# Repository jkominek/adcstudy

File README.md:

# what is this?

A set of kicad 8 boards for investigating various combinations of ADC
and analog frontend for my [piano
conversion](https://github.com/jkominek/piano-conversion) project.

There might be some errors and problems with them, but I'm not currently
aware of any issues.

# please describe the boards

The ADC boards are designed to plug into a [Glasgow Interface
Explorer](https://glasgow-embedded.org/latest/intro.html), but that's
done via 2.54mm pin headers, so you can hook them up to anything with
some jumper wires. The Glasgow header has the various digital signals
necessary for the board, and provides VDD. (Which the Glasgow can adjust.)
Whichever of my applets are complete-enough are available in
[my fork of the Glasgow repo](https://github.com/jkominek/glasgow).

The other side of the ADC board is designed to plug into an analog
frontend board. It should provide VAA to the AFE board, and receives
back Vref, and AINx+ and AINx-. + and/or - might be Vref, or ground,
or whatever. The ADC board might also ignore one or of the two and
reference the other to... whatever it wants. The MCP3008 board for
instance uses AINx- only, and references GND and Vref.

The AFE boards take in VAA, and produce Vref, along with the Ax+ and Ax-
signals. One of them will probably be fixed. In the middle it can do
whatever it wants, and then the other end should be a 2x8 connector
which (in my application) is used for 8 phototransistors. The positive
pin of each pair is intended for the collector, and the negative pin
for the emitter.

You can of course plug whatever you want into those pins.

# what's wrong with them

Haven't tested the ADS131M08 or resistor ladder boards yet,
though I did correct the systemic issues of which I was aware.

# what choices do the boards give me

You can put the headers on in whichever orientation you want, though if
you're hooking it up to a Glasgow like I am, there are only a couple
options that make sense.

The opamp footprint is the most common four amp footprint, so you can
stick any of a bunch of opamps in there.

There are a number of voltage reference ICs that'll work in the provided
footprint. I've been putting on MIC5366-2.0 because I have a bunch of
them.

The MCP3008 board lets you feed VDD through to VAA with just some passive
filtering, or you can put in a linear regulator.

Obviously you can swap the gain setting resistors.

# quick what's best

For these sorts of signals, the MCP6L04 seems good enough, with the
TSV994 probably a runner up because it is more expensive. A ~2870ohm
thin film gain resistor and a capacitor in parallel with that resistor
which is in the ballpark of 10nF. A bias resistor of about 470k to drain
off dark current is also indicated.

I've got some more ideas for tweaking the TIA configuration with just
passives.

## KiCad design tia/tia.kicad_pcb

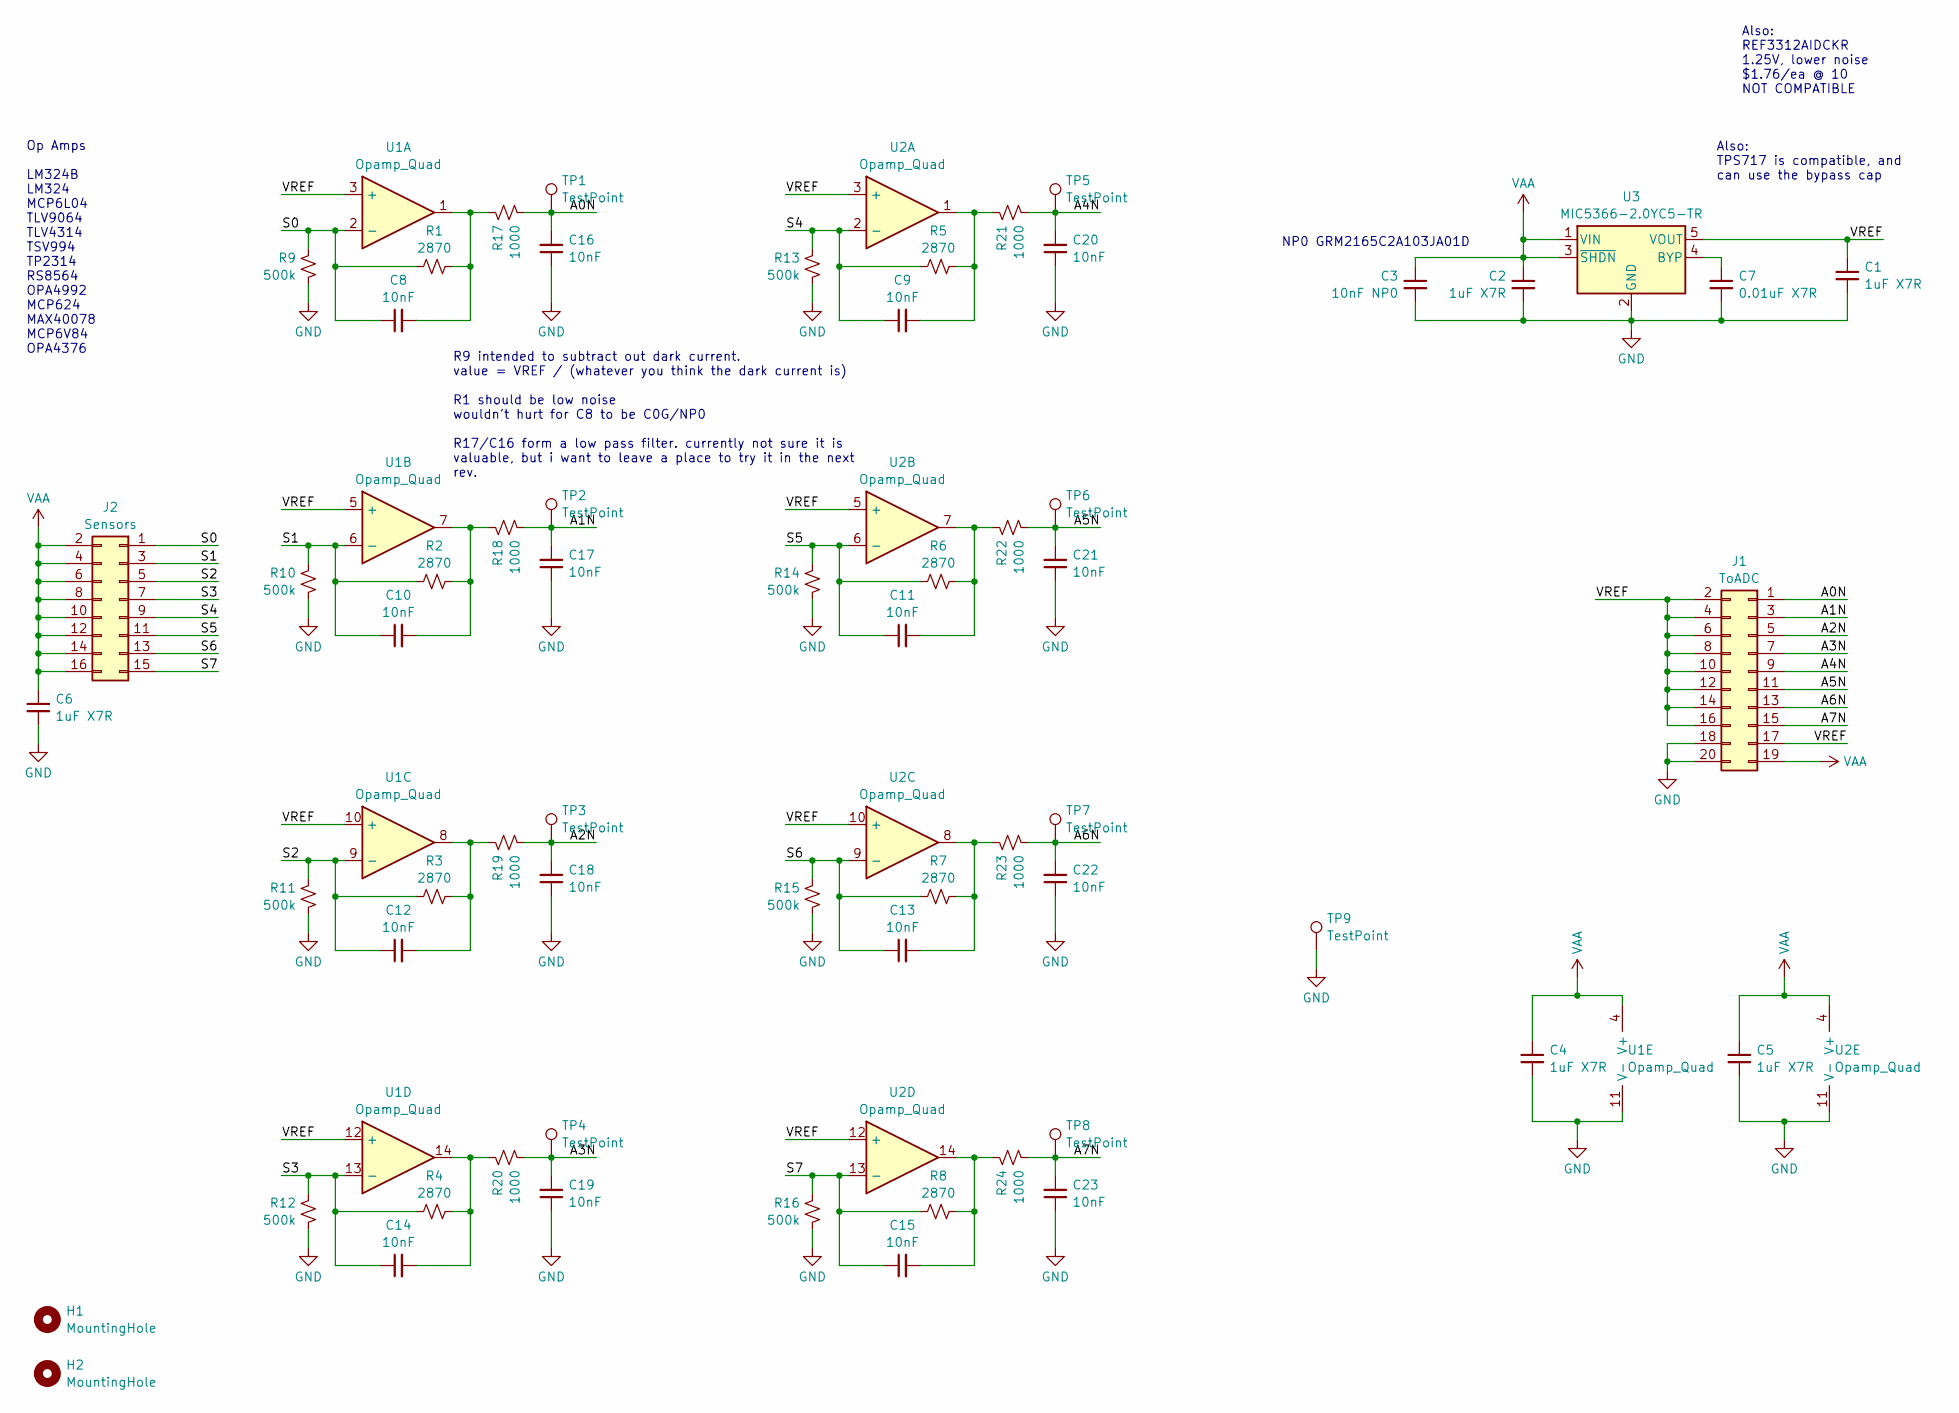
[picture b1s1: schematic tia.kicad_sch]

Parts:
C1, C2, C4, C5, C6: 1uF X7R; C_0805_2012Metric
C3: 10nF NP0; C_0805_2012Metric
C7: 0.01uF X7R; C_0805_2012Metric
C8, C9, C10, C11, C12, C13, C14, C15, C16, C17, C18, C19, C20, C21, C22, C23: 10nF; C_0805_2012Metric
H1, H2: MountingHole; MountingHole_3.2mm_M3
J1: ToADC; PinSocket_2x10_P2.54mm_Vertical
J2: Sensors; PinSocket_2x08_P2.54mm_Vertical
R1, R2, R3, R4, R5, R6, R7, R8: 2870; R_0805_2012Metric
R9, R10, R11, R12, R13, R14, R15, R16: 500k; R_0805_2012Metric
R17, R18, R19, R20, R21, R22, R23, R24: 1000; R_0805_2012Metric
TP1, TP2, TP3, TP4, TP5, TP6, TP7, TP8, TP9: TestPoint; TestPoint_Pad_D2.0mm
U1, U2: Opamp_Quad; TSSOP-14_4.4x5mm_P0.65mm
U3: MIC5366-2.0YC5-TR; SOT-353_SC-70-5

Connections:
/A0N: C16.2, J1.1, R17.1, TP1.1
/A1N: C17.2, J1.3, R18.1, TP2.1
/A2N: C18.2, J1.5, R19.1, TP3.1
/A3N: C19.2, J1.7, R20.1, TP4.1
/A4N: C20.2, J1.9, R21.1, TP5.1
/A5N: C21.2, J1.11, R22.1, TP6.1
/A6N: C22.2, J1.13, R23.1, TP7.1
/A7N: C23.2, J1.15, R24.1, TP8.1
/S0: C8.1, J2.1, R1.1, R9.2, U1.2 (-)
/S1: C10.1, J2.3, R2.1, R10.2, U1.6 (-)
/S2: C12.1, J2.5, R3.1, R11.2, U1.9 (-)
/S3: C14.1, J2.7, R4.1, R12.2, U1.13 (-)
/S4: C9.1, J2.9, R5.1, R13.2, U2.2 (-)
/S5: C11.1, J2.11, R6.1, R14.2, U2.6 (-)
/S6: C13.1, J2.13, R7.1, R15.2, U2.9 (-)
/S7: C15.1, J2.15, R8.1, R16.2, U2.13 (-)
/VREF: C1.1, J1.2, J1.4, J1.6, J1.8, J1.10, J1.12, J1.14, J1.16, J1.17, U1.3 (+), U1.5 (+), U1.10 (+), U1.12 (+), U2.3 (+), U2.5 (+), U2.10 (+), U2.12 (+), U3.5 (VOUT)
GND: C1.2, C2.2, C3.2, C4.2, C5.2, C6.2, C7.2, C16.1, C17.1, C18.1, C19.1, C20.1, C21.1, C22.1, C23.1, J1.18, J1.20, R9.1, R10.1, R11.1, R12.1, R13.1, R14.1, R15.1, R16.1, TP9.1, U1.11 (V-), U2.11 (V-), U3.2 (GND)
unnamed: C8.2, R1.2, R17.2, U1.1
unnamed: C9.2, R5.2, R21.2, U2.1
unnamed: C10.2, R2.2, R18.2, U1.7
unnamed: C11.2, R6.2, R22.2, U2.7
unnamed: C12.2, R3.2, R19.2, U1.8
unnamed: C13.2, R7.2, R23.2, U2.8
unnamed: C14.2, R4.2, R20.2, U1.14
unnamed: C15.2, R8.2, R24.2, U2.14
unnamed: C7.1, U3.4 (BYP)
VAA: C2.1, C3.1, C4.1, C5.1, C6.1, J1.19, J2.2, J2.4, J2.6, J2.8, J2.10, J2.12, J2.14, J2.16, U1.4 (V+), U2.4 (V+), U3.1 (VIN), U3.3 (~SHDN)

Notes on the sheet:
R9 intended to subtract out dark current. value = VREF / (whatever you think the dark current is) R1 should be low noise wouldn't hurt for C8 to be C0G/NP0 R17/C16 form a low pass filter. currently not sure it is valuable, but i want to leave a place to try it in the next rev.
Also: TPS717 is compatible, and can use the bypass cap
Also: REF3312AIDCKR 1.25V, lower noise $1.76/ea @ 10 NOT COMPATIBLE
Op Amps LM324B LM324 MCP6L04 TLV9064 TLV4314 TSV994 TP2314 RS8564 OPA4992 MCP624 MAX40078 MCP6V84 OPA4376
NP0 GRM2165C2A103JA01D

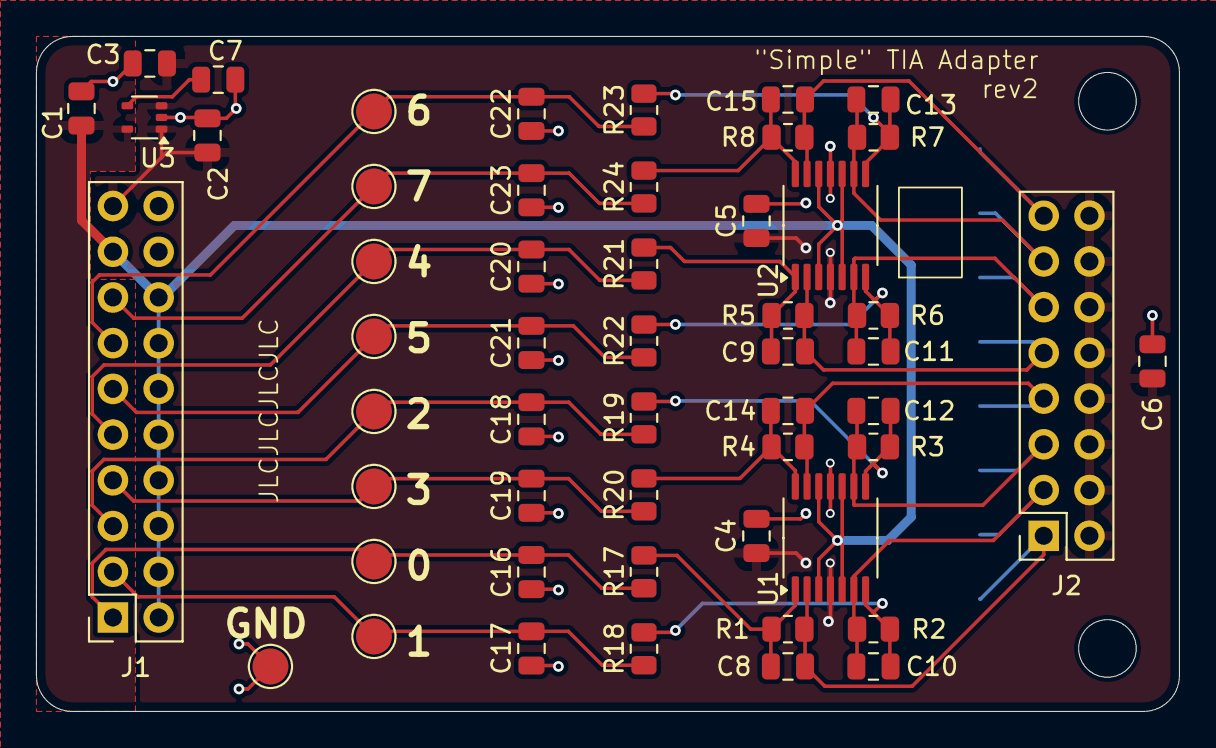
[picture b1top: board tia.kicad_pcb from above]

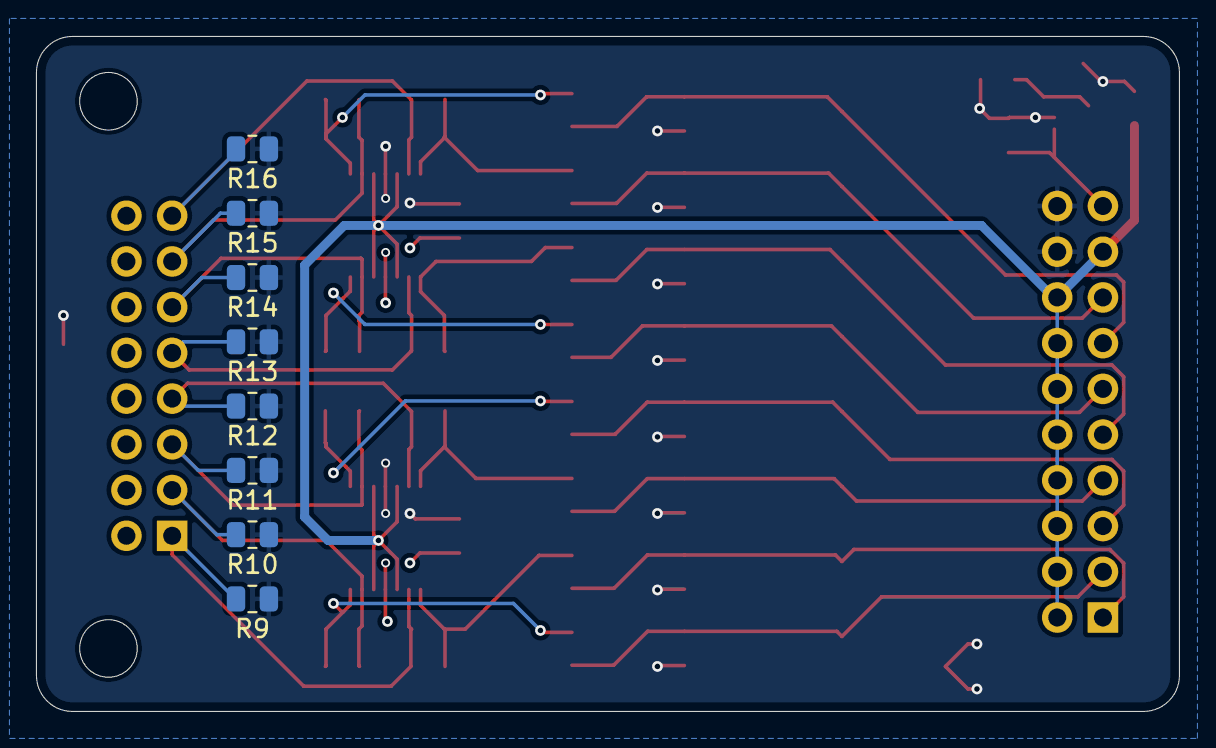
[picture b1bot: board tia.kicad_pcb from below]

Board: 4 copper layers, 63.5 x 37.5 mm, 63 parts (8 on the bottom side), 28 nets.

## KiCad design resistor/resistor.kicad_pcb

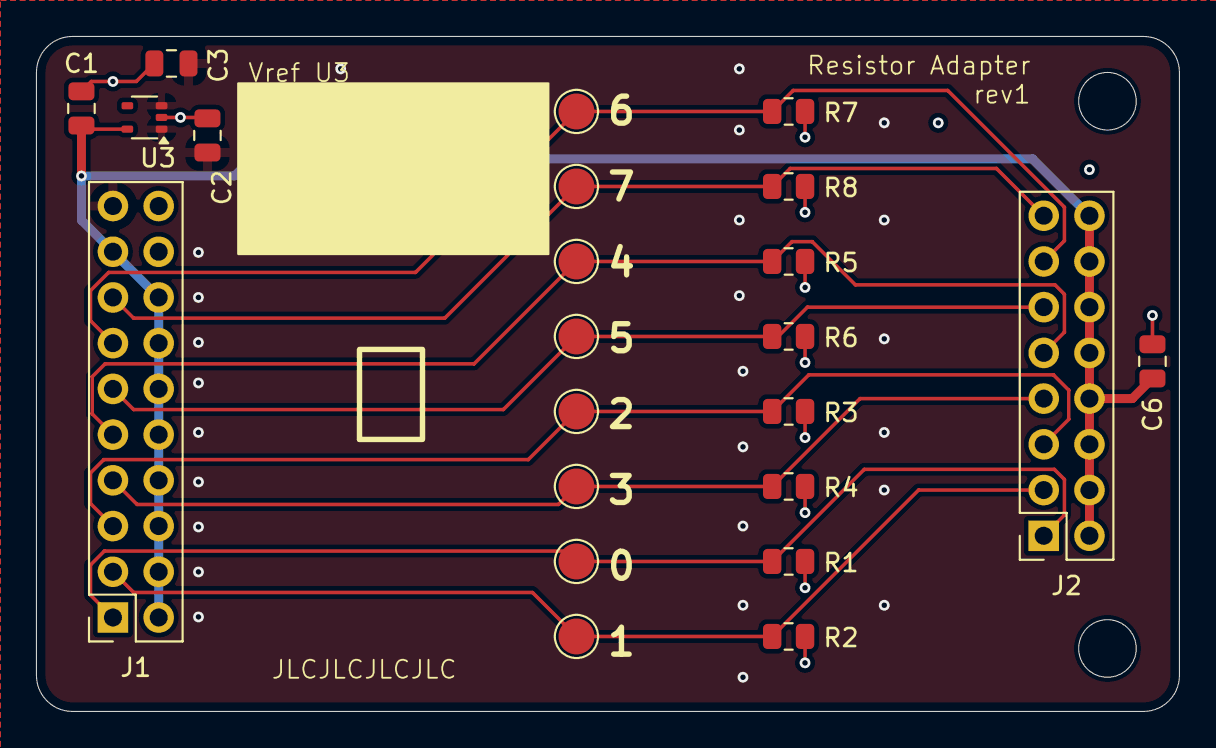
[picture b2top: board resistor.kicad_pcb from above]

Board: 4 copper layers, 63.5 x 37.5 mm, 25 parts (0 on the bottom side), 11 nets.

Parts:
C1, C2, C6: 1uF X7R; C_0805_2012Metric
C3: 10nF NP0; C_0805_2012Metric
H1, H2: MountingHole; MountingHole_3.2mm_M3
J1: ToADC; PinSocket_2x10_P2.54mm_Vertical
J2: Sensors; PinSocket_2x08_P2.54mm_Vertical
R1, R2, R3, R4, R5, R6, R7, R8: 1k; R_0805_2012Metric
TP1, TP2, TP3, TP4, TP5, TP6, TP7, TP8: TestPoint; TestPoint_Pad_D2.0mm
U3: MIC5366-2.0YC5-TR; SOT-353_SC-70-5

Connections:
/S0: J1.1, J2.1, R1.1, TP1.1
/S1: J1.3, J2.3, R2.1, TP2.1
/S2: J1.5, J2.5, R3.1, TP3.1
/S3: J1.7, J2.7, R4.1, TP4.1
/S4: J1.9, J2.9, R5.1, TP5.1
/S5: J1.11, J2.11, R6.1, TP6.1
/S6: J1.13, J2.13, R7.1, TP7.1
/S7: J1.15, J2.15, R8.1, TP8.1
/VREF: C1.1, C6.1, J1.2, J1.4, J1.6, J1.8, J1.10, J1.12, J1.14, J1.16, J1.17, J2.2, J2.4, J2.6, J2.8, J2.10, J2.12, J2.14, J2.16, U3.5 (VOUT)
GND: C1.2, C2.2, C3.2, C6.2, J1.18, J1.20, R1.2, R2.2, R3.2, R4.2, R5.2, R6.2, R7.2, R8.2, U3.2 (GND)
VAA: C2.1, C3.1, J1.19, U3.1 (VIN), U3.3 (~SHDN)

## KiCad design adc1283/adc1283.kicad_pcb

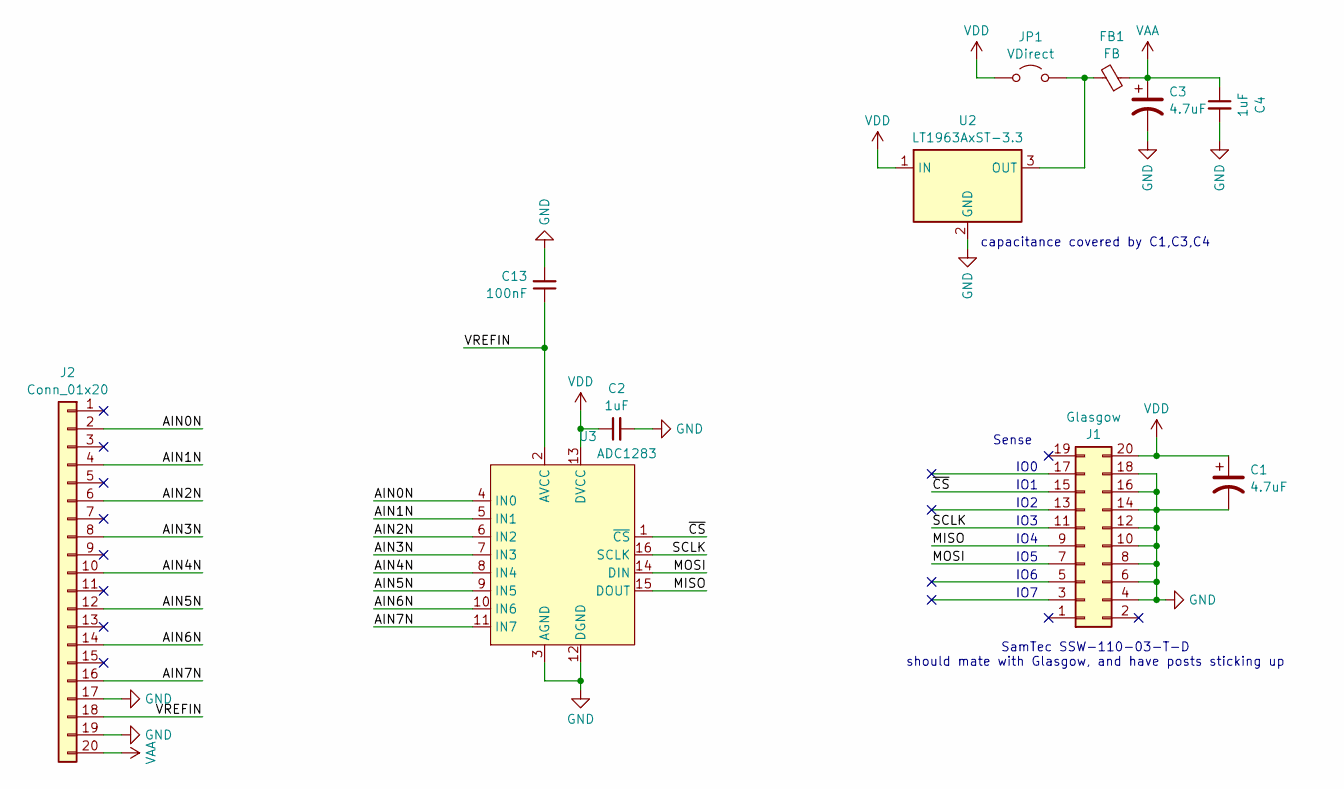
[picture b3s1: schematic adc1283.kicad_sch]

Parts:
C1, C3: 4.7uF; C_0805_2012Metric
C2, C4: 1uF; C_0805_2012Metric
C13: 100nF; C_0805_2012Metric
FB1: FB; L_0805_2012Metric
J1: Glasgow; PinHeader_2x10_P2.54mm_Vertical; DigiKey SSW-110-03-T-D-ND
J2: Conn_01x20; PinHeader_2x10_P2.54mm_Vertical
JP1: VDirect; SolderJumper-2_P1.3mm_Open_RoundedPad1.0x1.5mm
U2: LT1963AxST-3.3; SOT-223-3_TabPin2
U3: ADC1283; TSSOP-16_4.4x5mm_P0.65mm

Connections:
/AIN0N: J2.2, U3.4 (IN0)
/AIN1N: J2.4, U3.5 (IN1)
/AIN2N: J2.6, U3.6 (IN2)
/AIN3N: J2.8, U3.7 (IN3)
/AIN4N: J2.10, U3.8 (IN4)
/AIN5N: J2.12, U3.9 (IN5)
/AIN6N: J2.14, U3.10 (IN6)
/AIN7N: J2.16, U3.11 (IN7)
/MISO: J1.9, U3.15 (DOUT)
/MOSI: J1.7, U3.14 (DIN)
/SCLK: J1.11, U3.16 (SCLK)
/VREFIN: C13.1, J2.18, U3.2 (AVCC)
/~CS: J1.15, U3.1 (~CS)
GND: C1.2, C2.2, C3.2, C4.2, C13.2, J1.4, J1.6, J1.8, J1.10, J1.12, J1.14, J1.16, J1.18, J2.17, J2.19, U2.2 (GND), U3.3 (AGND), U3.12 (DGND)
unnamed: FB1.2, JP1.2 (B), U2.3 (OUT)
VAA: C3.1, C4.1, FB1.1, J2.20
VDD: C1.1, C2.1, J1.20, JP1.1 (A), U2.1 (IN), U3.13 (DVCC)

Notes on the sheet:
IO3
IO6
IO5
Sense
IO7
SamTec SSW-110-03-T-D should mate with Glasgow, and have posts sticking up
IO2
capacitance covered by C1,C3,C4
IO4
IO1
IO0

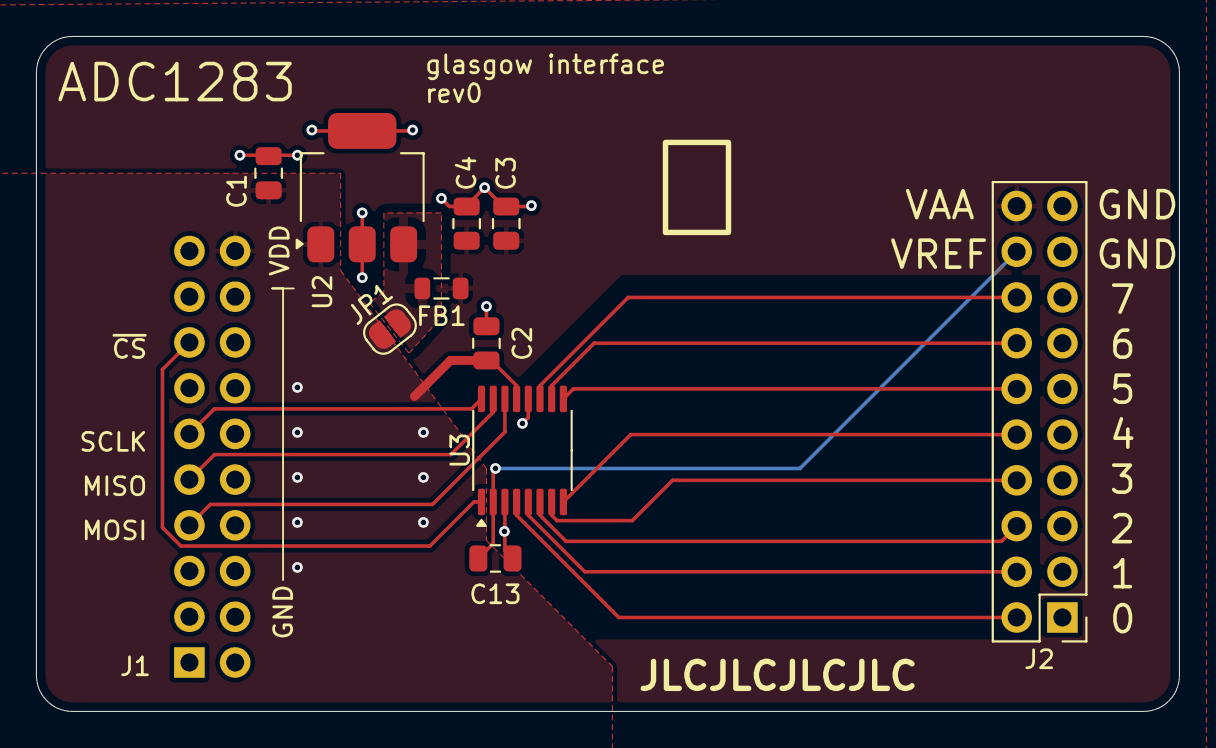
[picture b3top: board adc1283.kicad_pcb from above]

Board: 4 copper layers, 63.5 x 37.5 mm, 11 parts (1 on the bottom side), 17 nets.

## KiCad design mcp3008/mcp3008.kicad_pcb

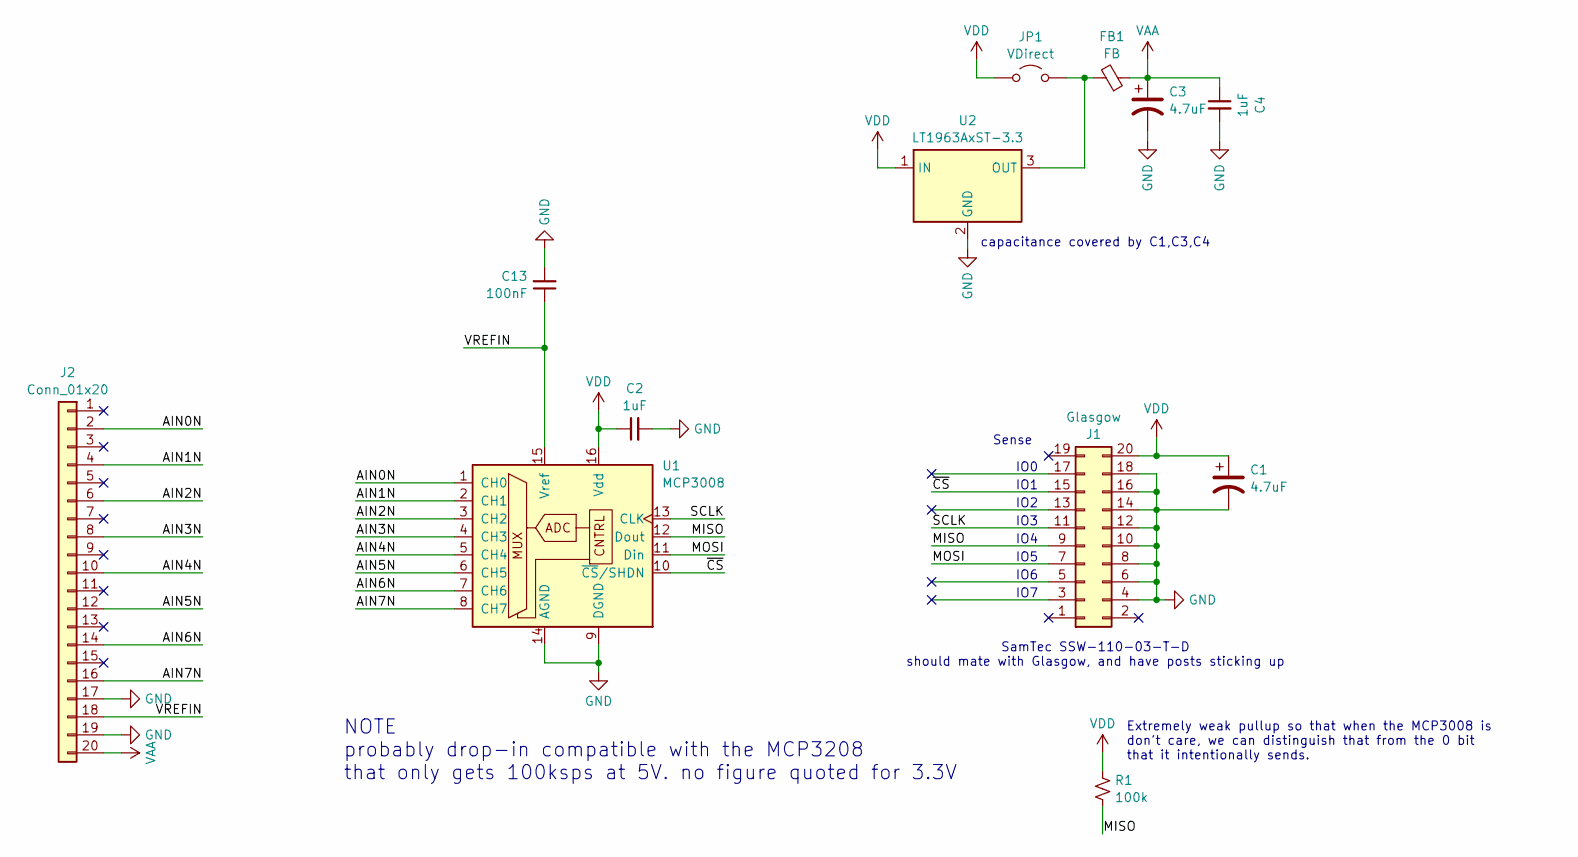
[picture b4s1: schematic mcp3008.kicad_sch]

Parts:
C1, C3: 4.7uF; C_0805_2012Metric
C2, C4: 1uF; C_0805_2012Metric
C13: 100nF; C_0805_2012Metric
FB1: FB; L_0805_2012Metric
J1: Glasgow; PinHeader_2x10_P2.54mm_Vertical; DigiKey SSW-110-03-T-D-ND
J2: Conn_01x20; PinHeader_2x10_P2.54mm_Vertical
JP1: VDirect; SolderJumper-2_P1.3mm_Open_RoundedPad1.0x1.5mm
R1: 100k; R_0805_2012Metric
U1: MCP3008; SOIC-16_3.9x9.9mm_P1.27mm
U2: LT1963AxST-3.3; SOT-223-3_TabPin2

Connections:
/AIN0N: J2.2, U1.1 (CH0)
/AIN1N: J2.4, U1.2 (CH1)
/AIN2N: J2.6, U1.3 (CH2)
/AIN3N: J2.8, U1.4 (CH3)
/AIN4N: J2.10, U1.5 (CH4)
/AIN5N: J2.12, U1.6 (CH5)
/AIN6N: J2.14, U1.7 (CH6)
/AIN7N: J2.16, U1.8 (CH7)
/MISO: J1.9, R1.2, U1.12 (Dout)
/MOSI: J1.7, U1.11 (Din)
/SCLK: J1.11, U1.13 (CLK)
/VREFIN: C13.1, J2.18, U1.15 (Vref)
/~CS: J1.15, U1.10 (~CS/SHDN)
GND: C1.2, C2.2, C3.2, C4.2, C13.2, J1.4, J1.6, J1.8, J1.10, J1.12, J1.14, J1.16, J1.18, J2.17, J2.19, U1.9 (DGND), U1.14 (AGND), U2.2 (GND)
unnamed: FB1.2, JP1.2 (B), U2.3 (OUT)
VAA: C3.1, C4.1, FB1.1, J2.20
VDD: C1.1, C2.1, J1.20, JP1.1 (A), R1.1, U1.16 (Vdd), U2.1 (IN)

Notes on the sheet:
IO3
IO6
IO5
Sense
IO7
SamTec SSW-110-03-T-D should mate with Glasgow, and have posts sticking up
IO2
Extremely weak pullup so that when the MCP3008 is don't care, we can distinguish that from the 0 bit that it intentionally sends.
capacitance covered by C1,C3,C4
IO4
IO1
IO0
NOTE probably drop-in compatible with the MCP3208 that only gets 100ksps at 5V. no figure quoted for 3.3V

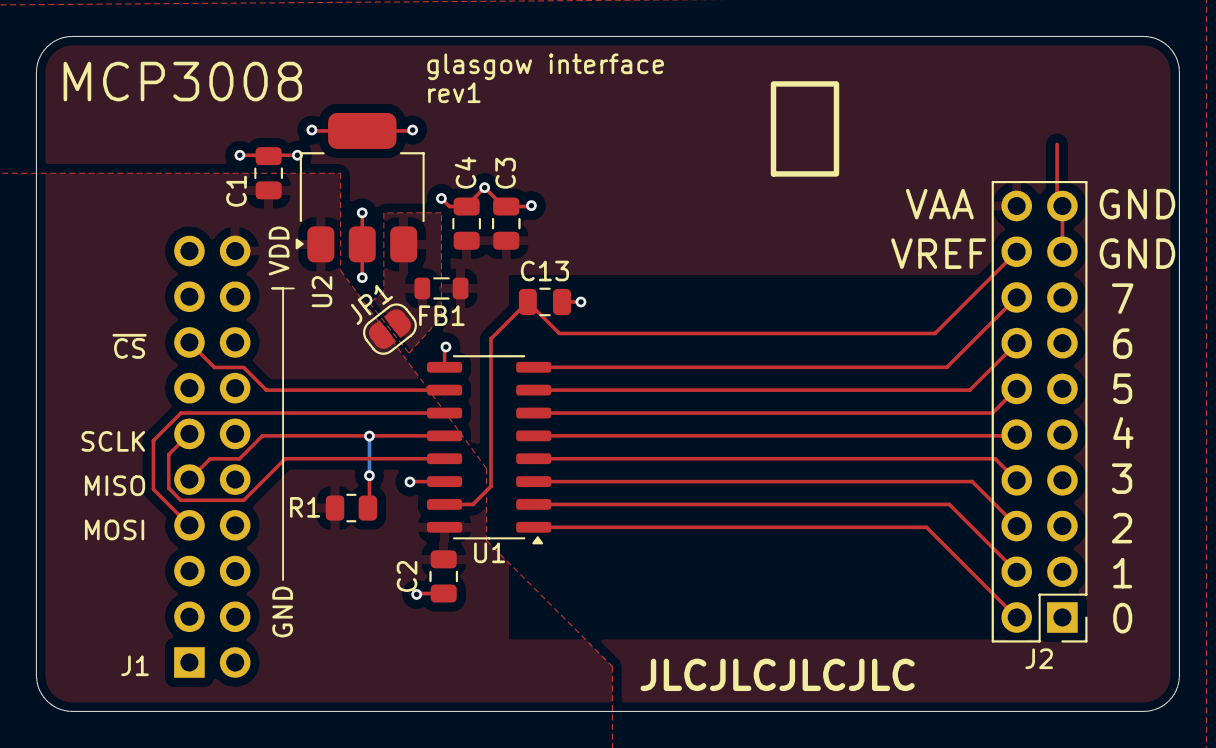
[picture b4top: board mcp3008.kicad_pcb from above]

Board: 4 copper layers, 63.5 x 37.5 mm, 12 parts (1 on the bottom side), 17 nets.

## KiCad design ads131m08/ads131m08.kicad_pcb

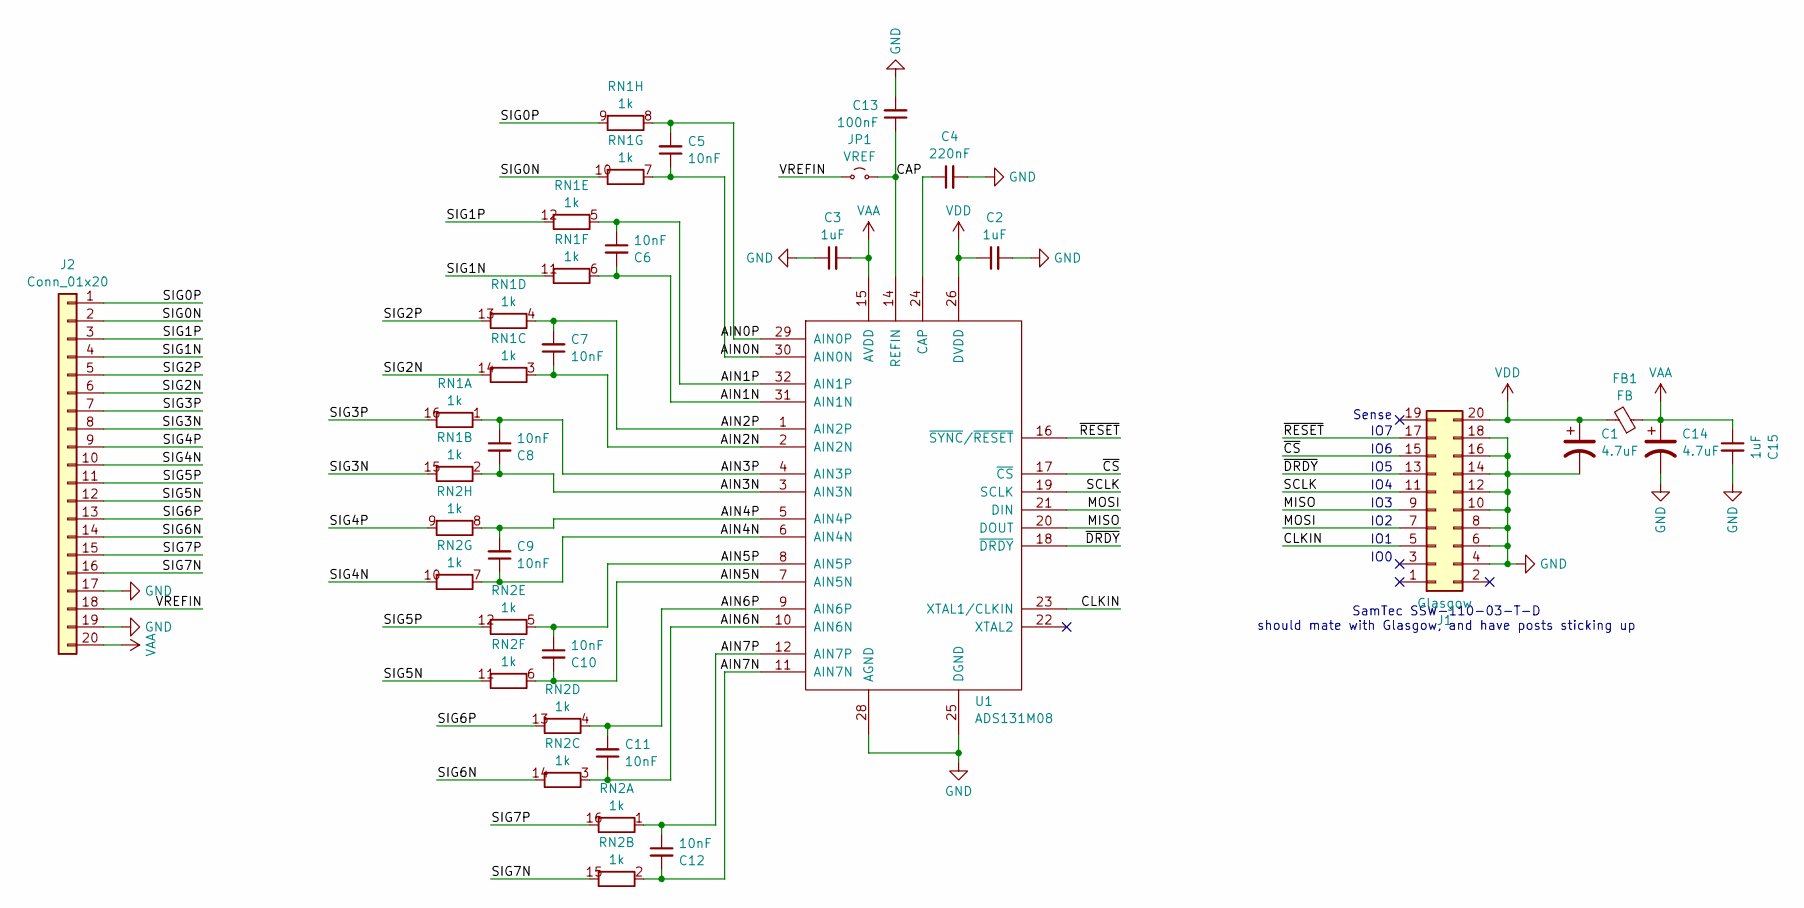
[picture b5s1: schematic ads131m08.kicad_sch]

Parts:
C1, C14: 4.7uF; C_0805_2012Metric
C2, C3, C15: 1uF; C_0805_2012Metric
C4: 220nF; C_0805_2012Metric
C5, C6, C7, C8, C9, C10, C11, C12: 10nF; C_0805_2012Metric
C13: 100nF; C_0805_2012Metric
FB1: FB; L_0805_2012Metric
J1: Glasgow; PinHeader_2x10_P2.54mm_Vertical; DigiKey SSW-110-03-T-D-ND
J2: Conn_01x20; PinHeader_2x10_P2.54mm_Vertical
JP1: VREF; PinHeader_1x02_P2.54mm_Vertical
RN1, RN2: 1k; SOIC-16_4.55x10.3mm_P1.27mm
U1: ADS131M08; LQFP-32_5x5mm_P0.5mm

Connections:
/AIN0N: C5.1, RN1.7 (R7.1), U1.30 (AIN0N)
/AIN0P: C5.2, RN1.8 (R8.1), U1.29 (AIN0P)
/AIN1N: C6.2, RN1.6 (R6.1), U1.31 (AIN1N)
/AIN1P: C6.1, RN1.5 (R5.1), U1.32 (AIN1P)
/AIN2N: C7.1, RN1.3 (R3.1), U1.2 (AIN2N)
/AIN2P: C7.2, RN1.4 (R4.1), U1.1 (AIN2P)
/AIN3N: C8.2, RN1.2 (R2.1), U1.3 (AIN3N)
/AIN3P: C8.1, RN1.1 (R1.1), U1.4 (AIN3P)
/AIN4N: C9.1, RN2.7 (R7.1), U1.6 (AIN4N)
/AIN4P: C9.2, RN2.8 (R8.1), U1.5 (AIN4P)
/AIN5N: C10.2, RN2.6 (R6.1), U1.7 (AIN5N)
/AIN5P: C10.1, RN2.5 (R5.1), U1.8 (AIN5P)
/AIN6N: C11.1, RN2.3 (R3.1), U1.10 (AIN6N)
/AIN6P: C11.2, RN2.4 (R4.1), U1.9 (AIN6P)
/AIN7N: C12.2, RN2.2 (R2.1), U1.11 (AIN7N)
/AIN7P: C12.1, RN2.1 (R1.1), U1.12 (AIN7P)
/CAP: C4.1, U1.24 (CAP)
/CLKIN: J1.5, U1.23 (XTAL1/CLKIN)
/MISO: J1.9, U1.20 (DOUT)
/MOSI: J1.7, U1.21 (DIN)
/SCLK: J1.11, U1.19 (SCLK)
/SIG0N: J2.2, RN1.10 (R7.2)
/SIG0P: J2.1, RN1.9 (R8.2)
/SIG1N: J2.4, RN1.11 (R6.2)
/SIG1P: J2.3, RN1.12 (R5.2)
/SIG2N: J2.6, RN1.14 (R3.2)
/SIG2P: J2.5, RN1.13 (R4.2)
/SIG3N: J2.8, RN1.15 (R2.2)
/SIG3P: J2.7, RN1.16 (R1.2)
/SIG4N: J2.10, RN2.10 (R7.2)
/SIG4P: J2.9, RN2.9 (R8.2)
/SIG5N: J2.12, RN2.11 (R6.2)
/SIG5P: J2.11, RN2.12 (R5.2)
/SIG6N: J2.14, RN2.14 (R3.2)
/SIG6P: J2.13, RN2.13 (R4.2)
/SIG7N: J2.16, RN2.15 (R2.2)
/SIG7P: J2.15, RN2.16 (R1.2)
/VREFIN: J2.18, JP1.1 (A)
/~CS: J1.15, U1.17 (~CS)
/~DRDY: J1.13, U1.18 (~DRDY)
/~RESET: J1.17, U1.16 (~SYNC/~RESET)
GND: C1.2, C2.2, C3.1, C4.2, C13.2, C14.2, C15.2, J1.4, J1.6, J1.8, J1.10, J1.12, J1.14, J1.16, J1.18, J2.17, J2.19, U1.13 (AGND), U1.25 (DGND), U1.28 (AGND)
unnamed: C13.1, JP1.2 (B), U1.14 (REFIN)
VAA: C3.2, C14.1, C15.1, FB1.1, J2.20, U1.15 (AVDD)
VDD: C1.1, C2.1, FB1.2, J1.20, U1.26 (DVDD)

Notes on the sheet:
IO3
IO6
IO5
Sense
IO7
SamTec SSW-110-03-T-D should mate with Glasgow, and have posts sticking up
IO2
IO4
IO1
IO0

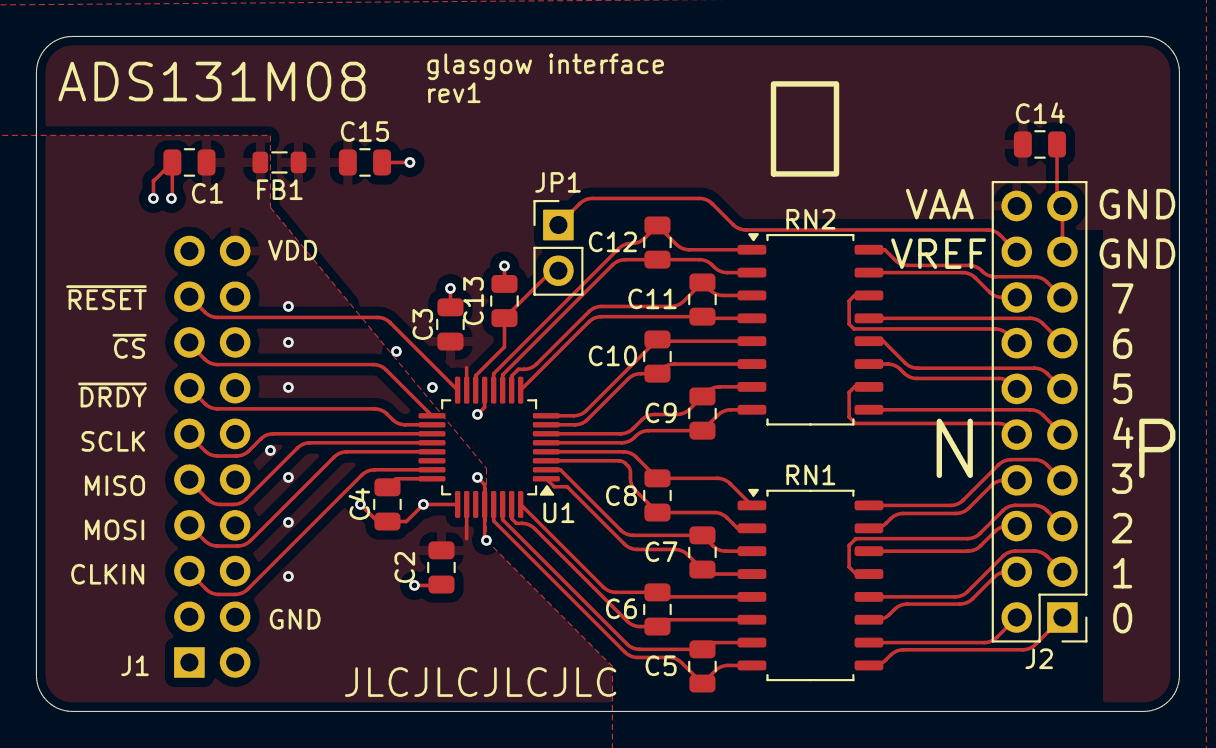
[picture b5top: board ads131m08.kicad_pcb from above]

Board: 4 copper layers, 63.5 x 37.5 mm, 22 parts (1 on the bottom side), 45 nets.

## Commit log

2024-05-17 rev0s of all the boards
2024-05-17 bit of a TODO list, so you know what's coming
2024-05-17 store some datasheets in here, so i don't keep searching for them
2024-05-21 bunch of collected data
2024-05-21 clarification
2024-05-22 notes on the first tests with the MCP3008
2024-05-23 more data, more notes
2024-06-01 filename fixes and thin film resistor data
2024-06-01 TIA cheap feedback resistor + capacitor data and notes
2024-06-01 more data, TIAs w/2870 thin film + notes
2024-06-02 0-1pF tests 6L04 and TLV9064
2024-06-02 TLV4314 and TSV994 data and notes
2024-06-03 ongoing data collection and ruminating in the notes file
2024-06-03 larger caps on signal seem to produce good results
2024-06-03 board revs, updated README
2024-06-03 rev2 of tia board, with bias and LPF
2024-06-03 bias resistor experiment
2024-06-04 ADC1283 first data
2024-06-09 more data and notes from a few days ago
2025-04-20 kicad 9 and some tiny tweak to the pcb i forgot about
2025-04-20 include TPS717 datasheet
2025-04-20 note bias resistor in README conclusion; bring TODO up to date
